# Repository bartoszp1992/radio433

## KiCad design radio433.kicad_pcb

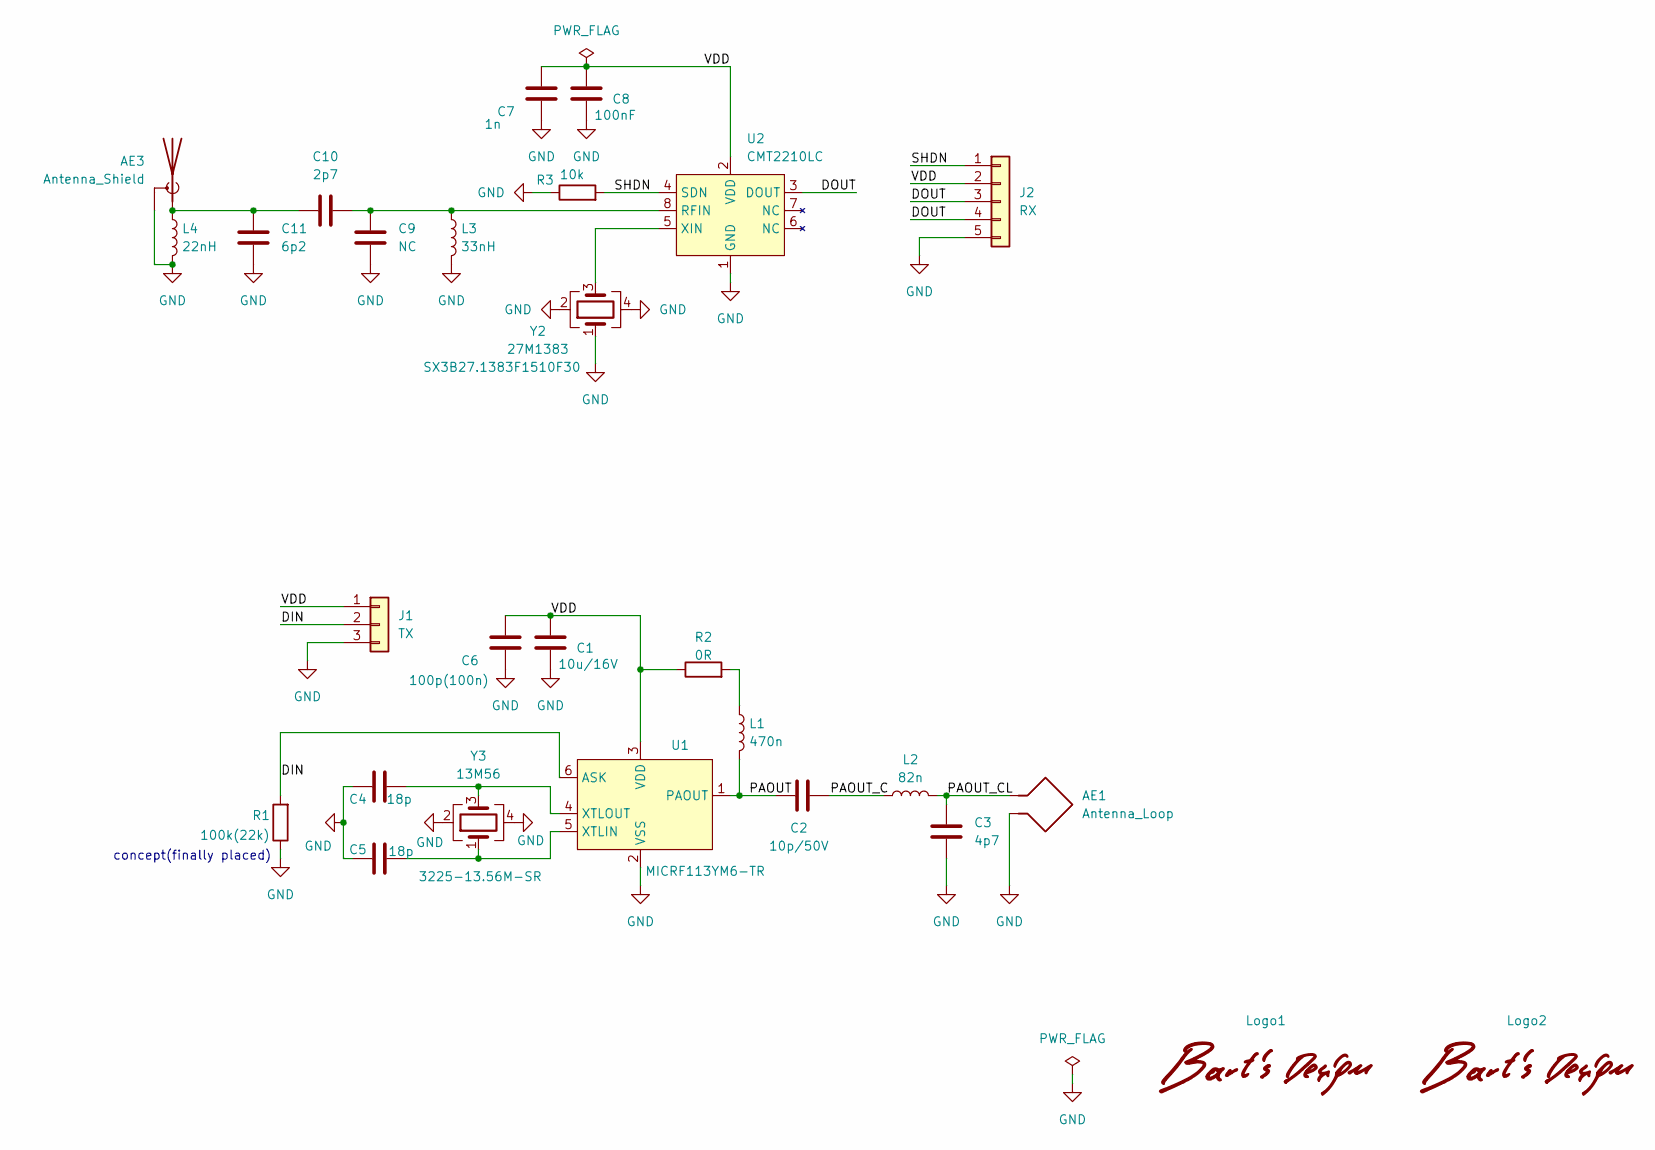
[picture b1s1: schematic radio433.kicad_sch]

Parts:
AE1: Antenna_Loop; antenna_433_50R_loop
AE3: Antenna_Shield; PinSocket_1x02_P2.54mm_Vertical
C1: 10u/16V; C_0805_2012Metric
C2: 10p/50V; C_0603_1608Metric
C3: 4p7; C_0603_1608Metric
C4, C5: 18p; C_0603_1608Metric
C6: 100p(100n); C_0603_1608Metric
C7: 1n; C_0603_1608Metric
C8: 100nF; C_0805_2012Metric
C9: NC; C_0603_1608Metric
C10: 2p7; C_0603_1608Metric
C11: 6p2; C_0603_1608Metric
J1: TX; PinHeader_1x03_P2.54mm_Vertical
J2: RX; PinHeader_1x05_P2.54mm_Vertical
L1: 470n; L_0603_1608Metric
L2: 82n; L_0603_1608Metric
L3: 33nH; L_0603_1608Metric
L4: 22nH; L_0603_1608Metric
Logo1, Logo2: Barts Design
R1: 100k(22k); L_0603_1608Metric
R2: 0R; L_0603_1608Metric
R3: 10k; R_0603_1608Metric
U1: MICRF113YM6-TR; SOT-23-6
U2: CMT2210LC; SO-8_3.9x4.9mm_P1.27mm
Y2: 27M1383; Crystal_SMD_3225-4Pin_3.2x2.5mm
Y3: 13M56; Crystal_SMD_3225-4Pin_3.2x2.5mm

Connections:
/DIN: J1.2, R1.2, U1.6 (ASK)
/DOUT: J2.3, J2.4, U2.3 (DOUT)
/PAOUT: C2.1, L1.2, U1.1 (PAOUT)
/PAOUT_C: C2.2, L2.1
/PAOUT_CL: AE1.1, C3.1, L2.2
/SHDN: J2.1, R3.2, U2.4 (SDN)
/VDD: C1.2, C6.1, C7.1, C8.2, J1.1, J2.2, R2.1, U1.3 (VDD), U2.2 (VDD)
GND: AE1.2, AE3.2 (Shield), C1.1, C3.2, C4.1, C5.1, C6.2, C7.2, C8.1, C9.2, C11.2, J1.3, J2.5, L3.2, L4.2, R1.1, R3.1, U1.2 (VSS), U2.1 (GND), Y2.1, Y2.2, Y2.4, Y3.2, Y3.4
unnamed: AE3.1 (A), C10.1, C11.1, L4.1
unnamed: L1.1, R2.2
unnamed: C5.2, U1.5 (XTLIN), Y3.1
unnamed: C4.2, U1.4 (XTLOUT), Y3.3
unnamed: C9.1, C10.2, L3.1, U2.8 (RFIN)
unnamed: U2.5 (XIN), Y2.3

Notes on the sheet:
concept(finally placed)

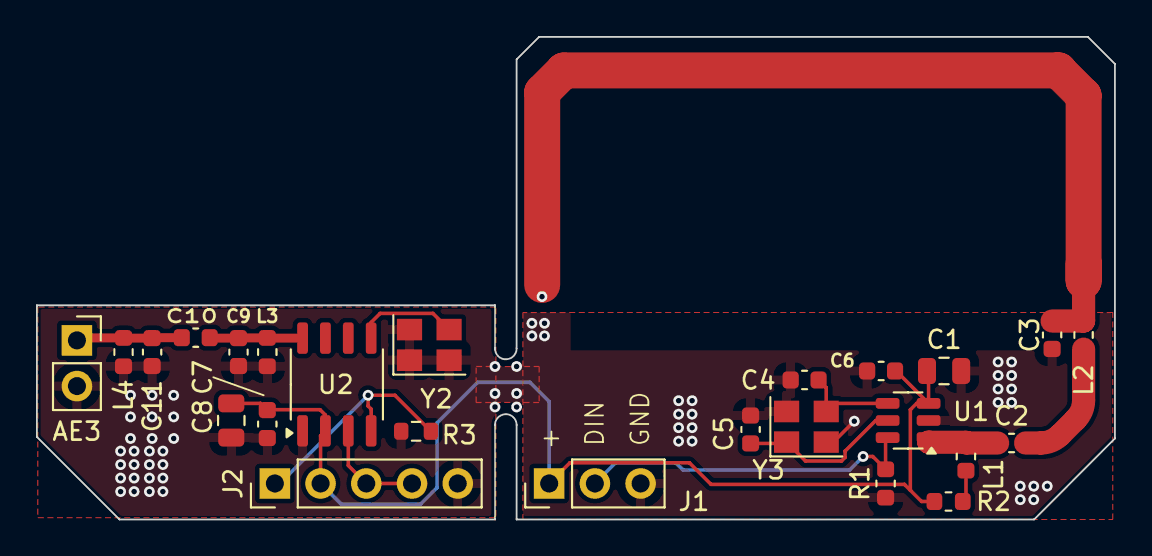
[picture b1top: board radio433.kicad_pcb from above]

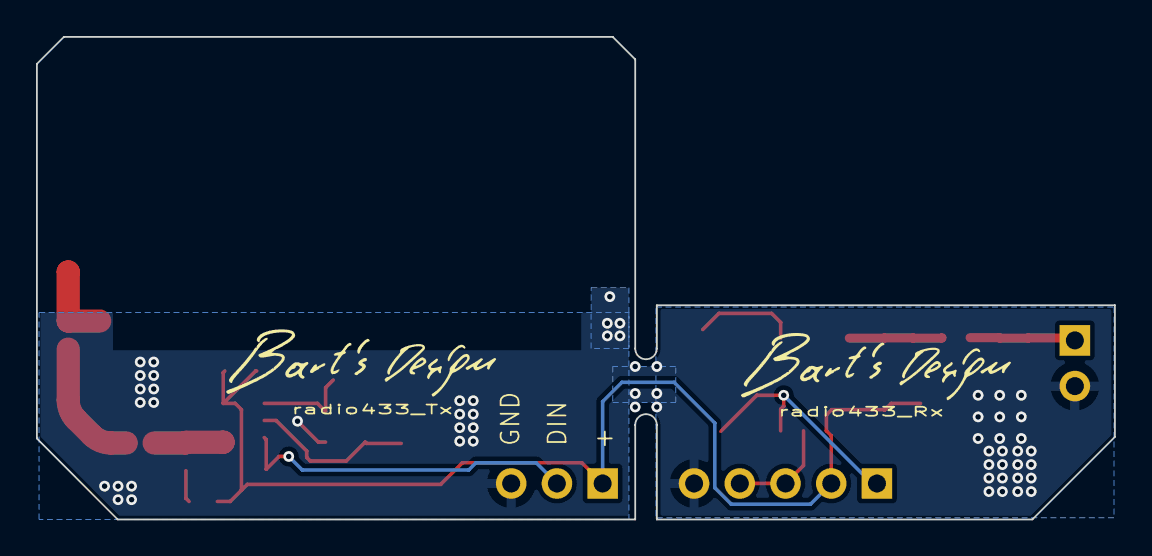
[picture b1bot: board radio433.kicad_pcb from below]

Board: 2 copper layers, 59.9 x 26.8 mm, 28 parts (2 on the bottom side), 14 nets.

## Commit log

2024-05-08 initial
2024-05-18 changed shape
2024-05-22 remover receiver
